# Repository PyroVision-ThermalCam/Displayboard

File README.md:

# PyroVision - Displayboard

## Table of Contents

- [PyroVision](#pyrovision)
  - [Table of Contents](#table-of-contents)
  - [About](#about)
  - [License](#license)
  - [Maintainer](#maintainer)

## About

Displayboard for the PyroVision Open-Source Thermal Camera.

## License

This project is licensed under the GNU General Public License v3.0. See the [LICENSE](LICENSE) file for details.

## Maintainer

- [Daniel Kampert](mailto:daniel.kampert@kampis-elektroecke.de)

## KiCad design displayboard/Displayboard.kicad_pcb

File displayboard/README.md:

<h1 align="center">PyroVision Mainboard</h1>

<p align="center" width="100%">
  
</p>

***

<p align="center">
  
&nbsp; &nbsp; &nbsp; &nbsp;
  
</p>

***

## SPECIFICATIONS

| Parameter | Value |
| --- | --- |
| Dimensions | 32.0 × 24.0 mm |

***

## DIRECTORY STRUCTURE

    .
    ├─ Computations       # Misc calculations
    ├─ HTML               # HTML files for generated webpage
    ├─ Images             # Pictures and renders
    │
    ├─ kibot_resources    # External resources for KiBot
    │  ├─ colors          # Color theme for KiCad
    │  ├─ fonts           # Fonts used in the project
    │  ├─ scripts         # External scripts used with KiBot
    │  └─ templates       # Templates for KiBot generated reports
    │
    ├─ kibot_yaml         # KiBot YAML config files
    ├─ KiRI               # KiRI (PCB diff viewer) files
    │
    ├─ lib                # KiCad footprint and symbol libraries
    │  ├─ 3d_models       # Component 3D models
    │  ├─ lib_fp          # Footprint libraries
    │  └─ lib_sym         # Symbol libraries
    │
    ├─ logos              # Logos
    │
    ├─ Manufacturing      # Assembly and fabrication documents
    │  ├─ Assembly        # Assembly documents (BoM, pos, notes)
    │  │
    │  └─ Fabrication     # Fabrication documents (ZIP, notes)
    │     ├─ Drill Tables # CSV drill tables
    │     └─ Gerbers      # Gerbers
    │
    ├─ Report             # Reports for ERC/DRC
    ├─ Schematic          # PDF of schematic
    ├─ templates          # Title block templates
    ├─ Testing
    │  └─ Testpoints      # Testpoints tables
    │
    └─ Variants           # Outputs for assembly variants

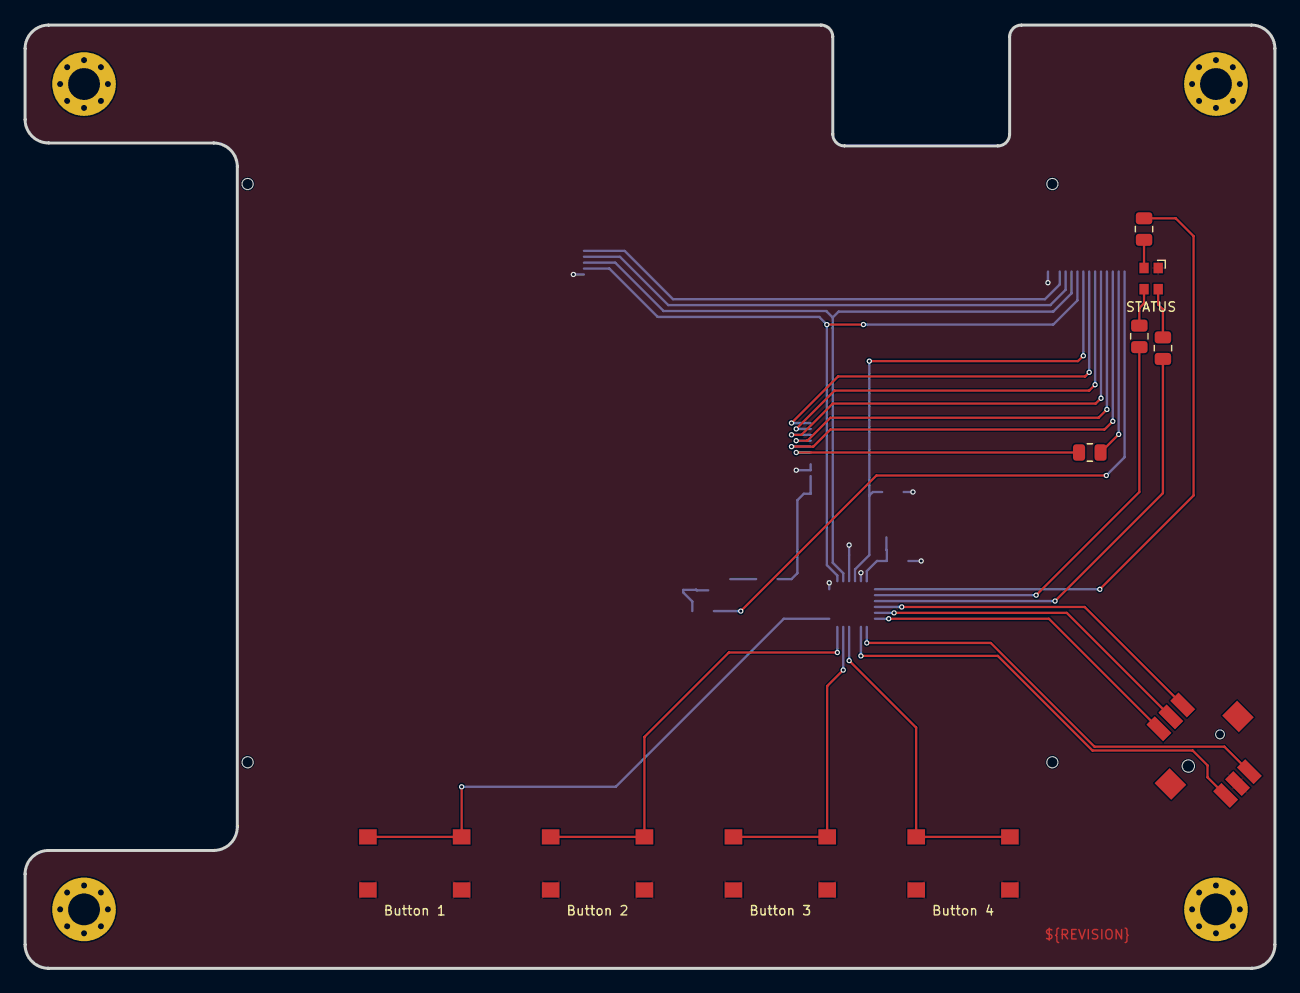
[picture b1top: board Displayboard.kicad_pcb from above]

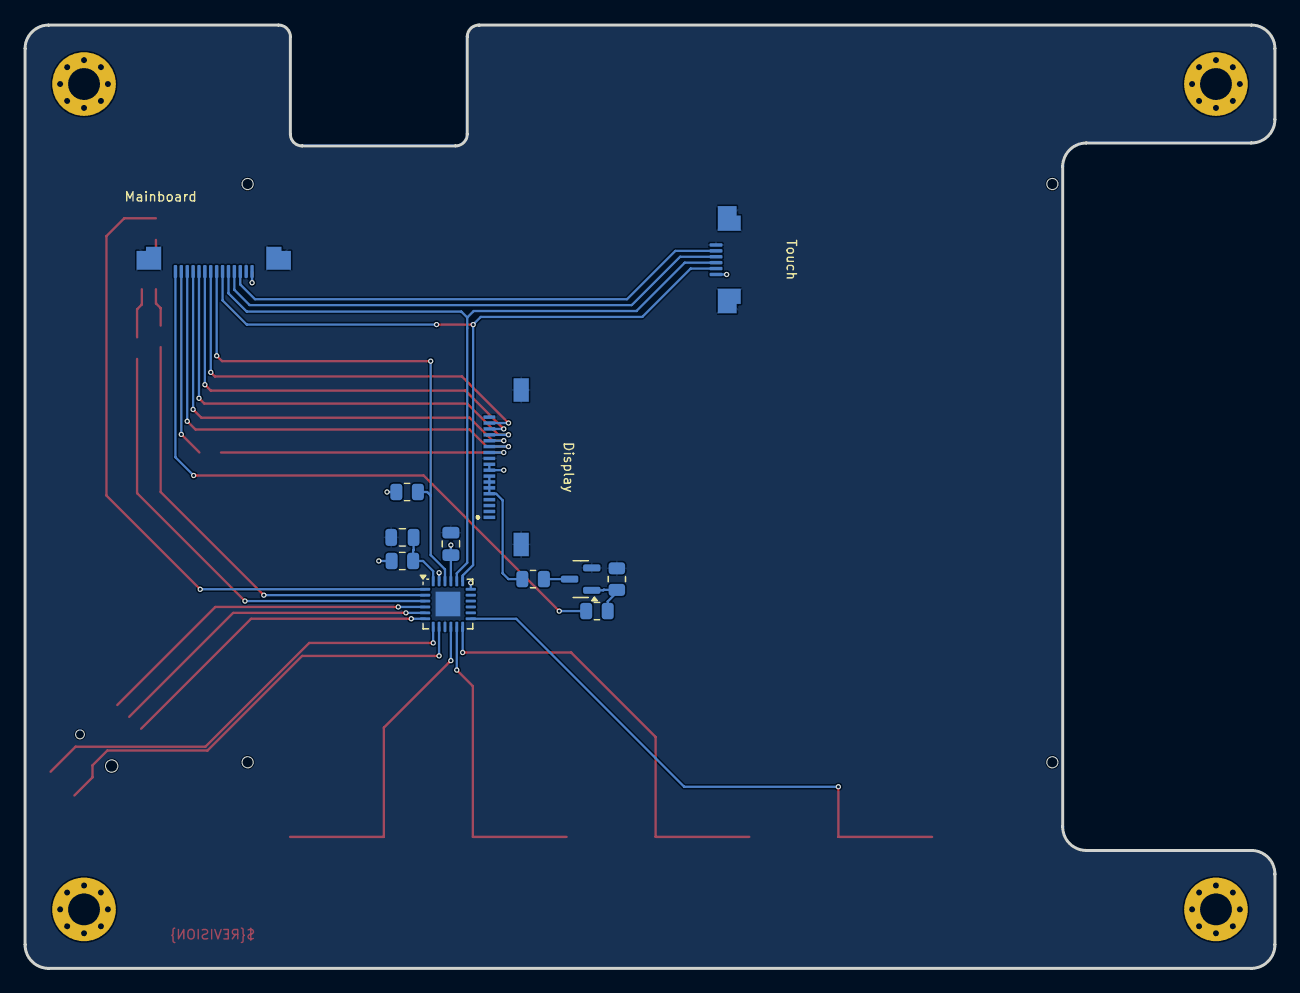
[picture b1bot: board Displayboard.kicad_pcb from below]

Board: 2 copper layers, 106.0 x 80.0 mm, 22 parts (12 on the bottom side), 34 nets.

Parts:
C401, C402: 100n; C_0805_2012Metric
D401: STATUS; LED_ASMB-KTF0-0A306
IC401: PCAL6416AHF; HVQFN-24-1EP_4x4mm_P0.5mm_EP2.1x2.1mm
Q501: NPN; SOT-23
R401, R503: 100k; R_0805_2012Metric
R402: 10k; R_0805_2012Metric
R403: 1k3; R_0805_2012Metric
R404: 330R; R_0805_2012Metric
R405: 470R; R_0805_2012Metric
R501: 0R; R_0805_2012Metric
R502: 10R; R_0805_2012Metric
R504: 100R; R_0805_2012Metric
S401: JS1400; JS1400BVQ
SW401: Button 1; WS-TASV-6x6
SW402: Button 2; WS-TASV-6x6
SW403: Button 3; WS-TASV-6x6
SW404: Button 4; WS-TASV-6x6
X501: Touch; Amphenol_F32R-1A7x1-11006_1x06-1MP_P0.5mm_Horizontal
X502: Display; 5051101892
X503: Mainboard; Amphenol_F32R-1A7x1-11014_1x14-1MP_P0.5mm_Horizontal

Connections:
+3V3: C402.1, D401.1 (A), IC401.18 (ADDR), IC401.21 (V_{DD(P)}), IC401.23 (V_{DD(I2C-bus)}), R401.2, R402.2, S401.5, SW401.2, SW401.4, SW402.2, SW402.4, SW403.2, SW403.4, SW404.2, SW404.4, X501.1, X502.9, X502.10, X503.1
/Project Architecture/Connectors/Display-Backlight: R504.1, X503.14
/Project Architecture/Connectors/Display-DC: X502.15, X503.10
/Project Architecture/Connectors/I2C-SCL: IC401.19 (SCL), X501.2, X503.6
/Project Architecture/Connectors/I2C-SDA: IC401.20 (SDA), X501.3, X503.5
/Project Architecture/Connectors/SPI-MISO: R501.1, X503.13
/Project Architecture/Connectors/SPI-MOSI: X502.13, X503.12
/Project Architecture/Connectors/SPI-SCLK: X502.16, X503.9
/Project Architecture/Connectors/~Display-CS: X502.14, X503.11
/Project Architecture/Connectors/~Display-Reset: X502.17, X503.8
/Project Architecture/Connectors/~Expander-Int: IC401.22 (~INT), R402.1, X503.7
/Project Architecture/Connectors/~Touch-IRQ: X501.4, X503.4
/Project Architecture/Connectors/~Touch-Reset: X501.5, X503.3
GND: C401.2, C402.2, IC401.9 (V_{SS}), IC401.25 (EP), Q501.2 (E), R503.1, X501.6, X501.MP (MountPin), X502.11, X502.18, X502.MP (MountPin), X503.2, X503.MP (MountPin)
unnamed: D401.2 (BK), R405.1
unnamed: D401.3 (GK), R404.1
unnamed: D401.4 (RK), R403.1
unnamed: IC401.1 (P0_0), R405.2
unnamed: IC401.2 (P0_1), R404.2
unnamed: IC401.3 (P0_2), R403.2
unnamed: IC401.4 (P0_3), S401.1
unnamed: IC401.5 (P0_4), S401.2
unnamed: IC401.6 (P0_5), S401.3
unnamed: IC401.7 (P0_6), S401.4
unnamed: IC401.8 (P0_7), S401.6
unnamed: IC401.10 (P1_0), SW404.1, SW404.3
unnamed: IC401.11 (P1_1), SW403.1, SW403.3
unnamed: IC401.12 (P1_2), SW402.1, SW402.3
unnamed: IC401.13 (P1_3), SW401.1, SW401.3
unnamed: C401.1, IC401.24 (~RESET), R401.1
unnamed: Q501.1 (B), R503.2, R504.2
unnamed: Q501.3 (C), R502.1
unnamed: R502.2, X502.5, X502.6, X502.7, X502.8
unnamed: R501.2, X502.12

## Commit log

2025-12-30 Initialize repository
2025-12-30 Initialize branch
2025-12-30 Push outputs from CI/CD (2025-12-30 10:58:06)
2026-01-07 Remove old production files, add cutout for the programming cable, add connector for mainboard cable
2026-01-07 Push outputs from CI/CD (2026-01-07 14:04:57)
2026-01-11 Increase cutout for programming connector
2026-01-11 Increase PCB size by 4 mm
2026-01-11 Add missing 3D models
2026-01-17 Prepare Release 1.0.0
2026-01-17 Release 1.0.0
2026-01-17 Update CHANGELOG
2026-01-17 Update outputs (release)
2026-01-17 Add GitHub automations for dev branch creation and a commit message template
2026-01-17 Initialize development branch for version 1.0.1
2026-04-15 Changed: Add missing part informations
2026-04-15 Bug: Issue #10
    - Update thomaseizinger/keep-a-changelog-new-release to version 3
    Closes #10
2026-04-15 Changed: Adjust dimensions
2026-04-15 Added: Add missing dimensions for the PCB size
2026-04-15 Feature: Issue #19
    - Replace JS1400BFQ with MU-BUE70R
    - Add CI/CD workflow to check for changelog updates on PRs
    Closes #19
2026-04-15 CI/CD fixes
2026-04-15 Feature: Add debounce capacitors to push buttons
    - Replace NPN transistor with N-Channel MOSFET
2026-04-15 Changed: Rework debouncing logic
2026-04-15 Added: Add a cutout for the display cable, add different assembly improvements
2026-04-16 CI/CD files updated for 1.0.1 release preparation
2026-05-30 Initialize development branch for version 1.0.2
2026-05-30 Fix wrong 3D model for button 4
2026-05-30 Update CHANGELOG workflow to latest version

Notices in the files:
README.md:
License: GPL 3.0
